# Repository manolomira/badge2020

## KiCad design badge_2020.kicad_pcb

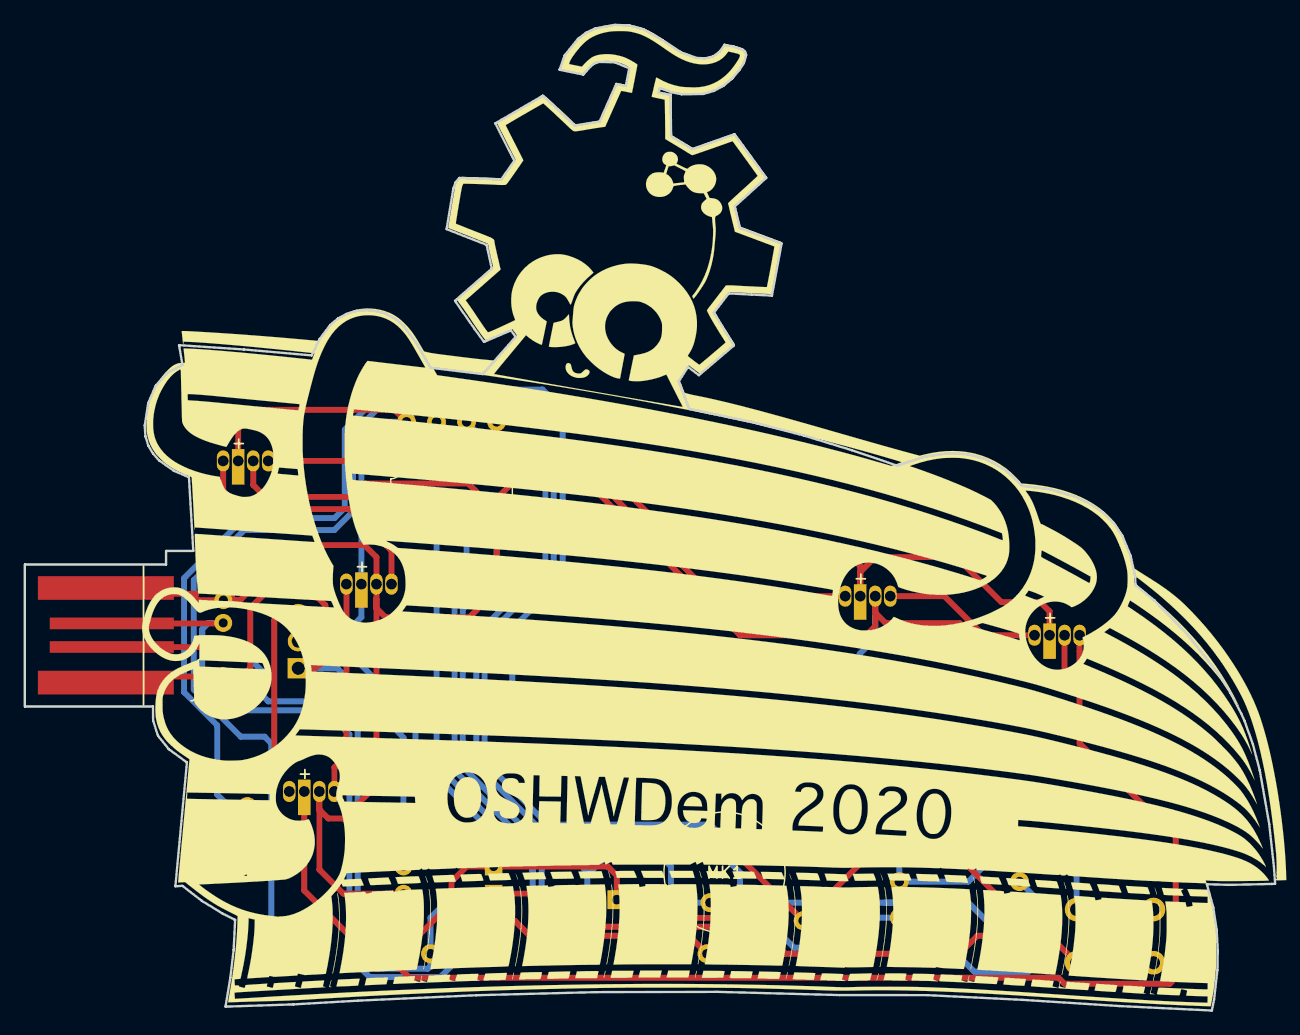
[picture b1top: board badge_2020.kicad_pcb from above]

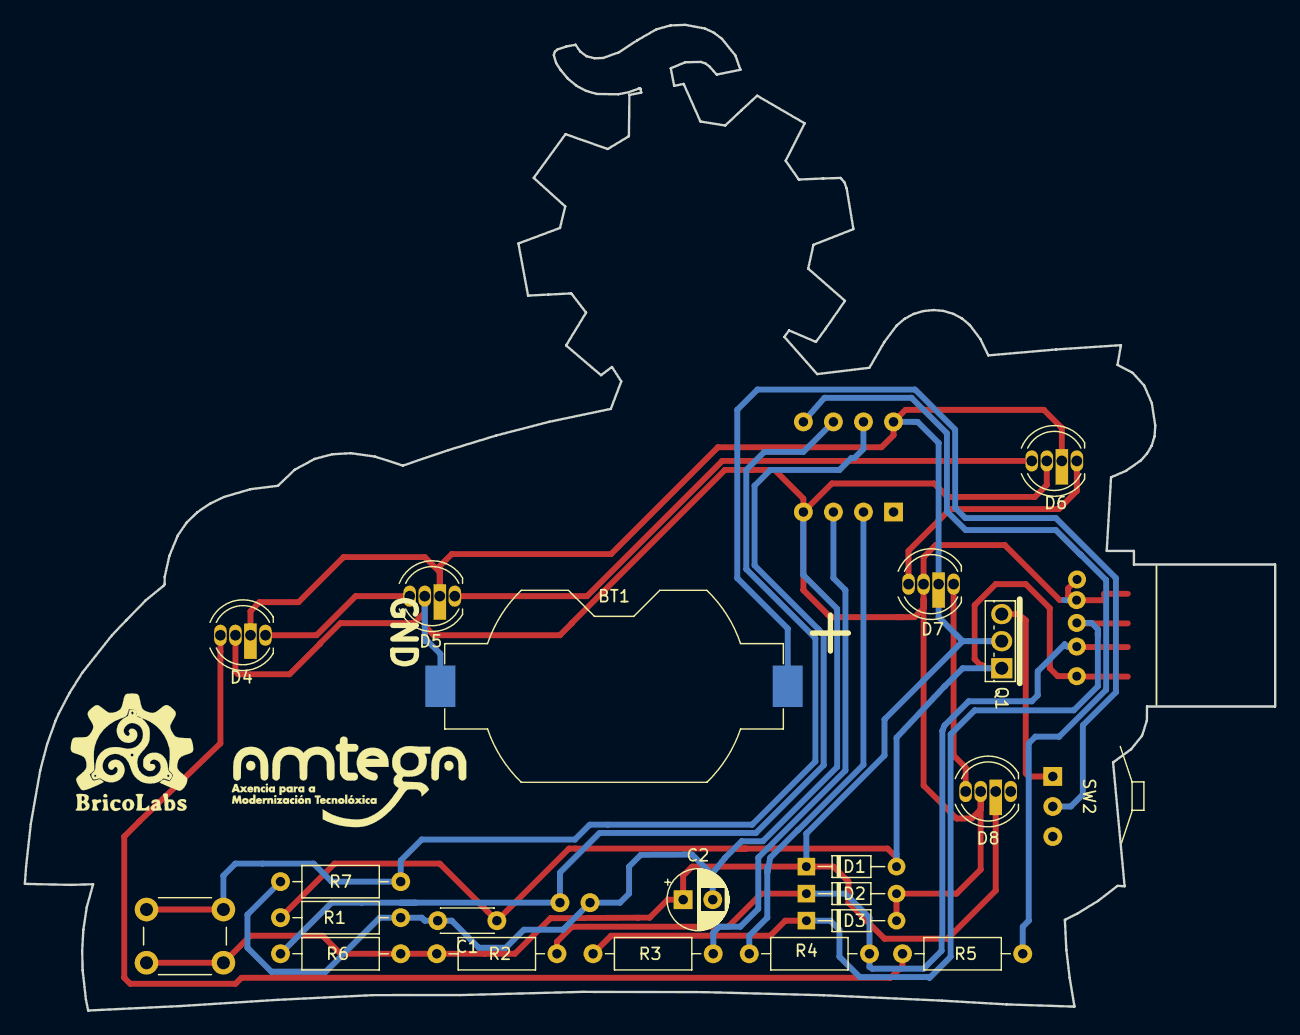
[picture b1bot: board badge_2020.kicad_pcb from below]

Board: 2 copper layers, 105.7 x 83.3 mm, 27 parts (23 on the bottom side), 17 nets.

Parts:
BT1: CR2032; BatteryHolder_Keystone_1058_1x2032
C1: 100K; C_Disc_D4.3mm_W1.9mm_P5.00mm
C2: 10uF; CP_Radial_D5.0mm_P2.50mm
D1: BAT41; D_DO-34_SOD68_P7.62mm_Horizontal
D2, D3: BZX55 3V6; D_DO-34_SOD68_P7.62mm_Horizontal
D4, D5, D6, D7, D8: WS2812D; LED_D5.0mm-WS2812D
Imagen_1: IMAGEN OSHWI; •OSHWI_footprint_silk
Imagen_2: LOGO AMTEGA; amtega_logo_2cm
Imagen_3: LOGO BRICOLABS; BricoLabs_logo_small
J1: USB_A; USB_A_onBoard
MK1: 0905P; Microphone_D10.0mm_P2.54mm
Q1: AOI409; TO-251-3_Vertical
R1: 100K; R_Axial_DIN0207_L6.3mm_D2.5mm_P10.16mm_Horizontal
R2: 1K5; R_Axial_DIN0207_L6.3mm_D2.5mm_P10.16mm_Horizontal
R3, R4: 68R; R_Axial_DIN0207_L6.3mm_D2.5mm_P10.16mm_Horizontal
R5: 470R; R_Axial_DIN0207_L6.3mm_D2.5mm_P10.16mm_Horizontal
R6, R7: 10K; R_Axial_DIN0207_L6.3mm_D2.5mm_P10.16mm_Horizontal
SW1: SW_Push; SW_PUSH_6mm_H4.3mm
SW2: SW; SW_DIP_SPDT_Slide_angled_ESP20XX
U1: ATTINY85-20PU; DIP-8_W7.62mm

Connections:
/D: Q1.3, SW2.1
GND: BT1.2, C1.2, C2.2, D2.2, D3.2, D4.3, D5.3, D6.3, D7.3, D8.3, J1.4, J1.5, MK1.1, R1.1, R7.1, U1.4
unnamed: BT1.1, SW2.2
unnamed: C1.1, D1.2, J1.1, Q1.1, R1.2
unnamed: C2.1, D1.1, D4.2, D5.2, D6.2, D7.2, D8.2, Q1.2, R2.2, R6.2, SW1.1, U1.8
unnamed: D2.1, J1.2, R2.1, R4.1
unnamed: D3.1, J1.3, R3.1
unnamed: D4.1, D5.4
unnamed: D4.4, R5.2
unnamed: D5.1, D6.4
unnamed: D6.1, D7.4
unnamed: D7.1, D8.4
unnamed: MK1.2, R6.1, U1.7
unnamed: R3.2, U1.3
unnamed: R4.2, U1.2
unnamed: R5.1, U1.5
unnamed: R7.2, SW1.2, U1.6

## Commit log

2020-10-08 comit inicial
2020-10-19 revisado y actualizado
    Esta versión debería funcionar. Falta el silkscreen posterior, y quizá cambiar la huella del interruptor
2020-10-19 Retoques menores
2020-10-20 Actualizado con trasera
2020-10-20 Añadidos ficheros Gerber
2020-11-16 Actualización
    Versión corregida y actualizada
